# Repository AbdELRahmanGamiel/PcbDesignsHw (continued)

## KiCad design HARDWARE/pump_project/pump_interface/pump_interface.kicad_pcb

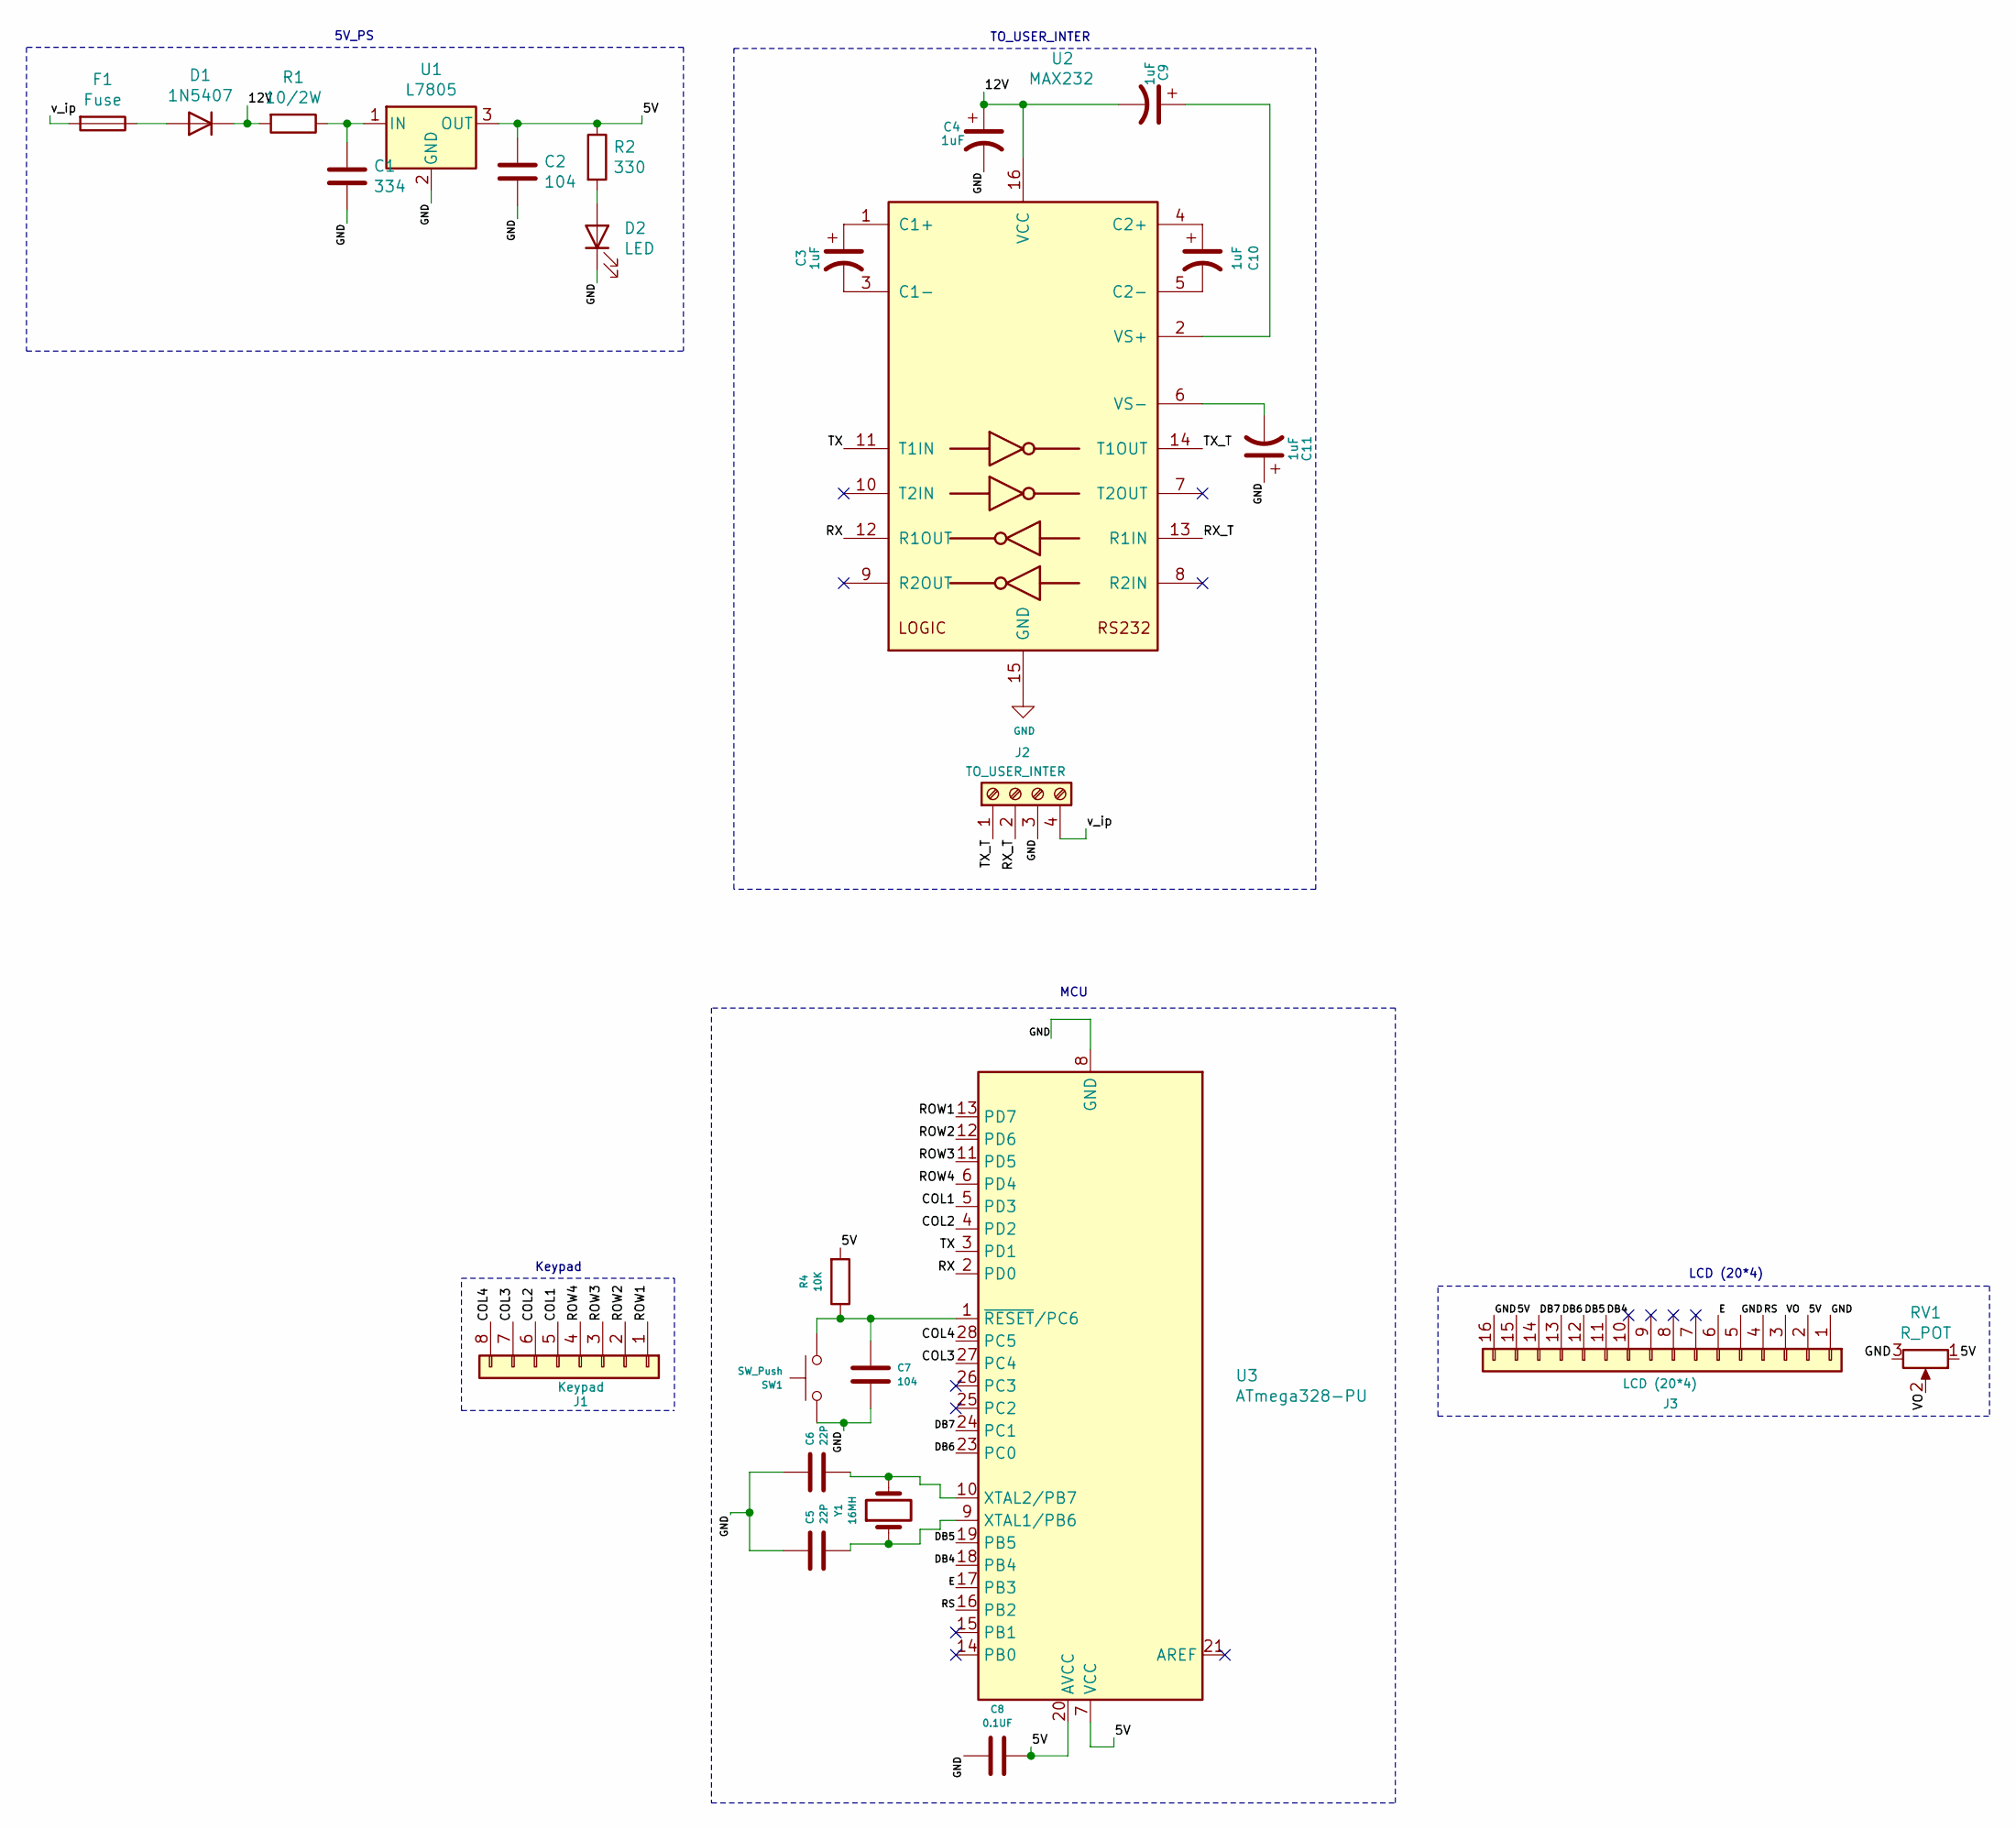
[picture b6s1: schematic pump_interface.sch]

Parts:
C1: 334; C_Disc_D7.0mm_W2.5mm_P5.00mm
C2, C7: 104; C_Disc_D7.0mm_W2.5mm_P5.00mm
C3, C4, C9, C10, C11: 1uF; C_Radial_D5.0mm_H5.0mm_P2.00mm
C5, C6: 22P; C_Disc_D7.0mm_W2.5mm_P5.00mm
C8: 0.1UF; C_Disc_D7.0mm_W2.5mm_P5.00mm
D1: 1N5407; D_DO-201AD_P15.24mm_Horizontal
D2: LED; LED_D5.0mm
F1: Fuse; Fuseholder_Cylinder-5x20mm_Schurter_0031_8201_Horizontal_Op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
J1: Keypad; PinHeader_1x08_P2.54mm_Vertical
J2: TO_USER_INTER; PhoenixContact_MSTBA_2,5_4-G-5,08_1x04_P5.08mm_Horizontal
J3: LCD (20*4); PinHeader_1x16_P2.54mm_Vertical
R1: 10/2W; R_Axial_Power_L20.0mm_W6.4mm_P25.40mm
R2: 330; R_Axial_DIN0207_L6.3mm_D2.5mm_P10.16mm_Horizontal
R4: 10K; R_Axial_DIN0207_L6.3mm_D2.5mm_P10.16mm_Horizontal
RV1: R_POT; Potentiometer_Bourns_3266Y_Vertical
SW1: SW_Push; SW_PUSH_6mm_H7.3mm
U1: L7805; TO-220-3_Vertical
U2: MAX232; DIP-16_W7.62mm_Socket_LongPads
U3: ATmega328-PU; DIP-28_W7.62mm
Y1: 16MH; Resonator-2Pin_W10.0mm_H5.0mm

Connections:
/5V: C2.1, C8.1, J3.2, J3.15, R2.1, R4.2, RV1.1, U1.3 (OUT), U3.7 (VCC), U3.20 (AVCC)
/12V: C4.1, C9.2, D1.1 (K), R1.2, U2.16 (VCC)
/COL1: J1.5, U3.5 (PD3)
/COL2: J1.6, U3.4 (PD2)
/COL3: J1.7, U3.27 (PC4)
/COL4: J1.8, U3.28 (PC5)
/DB4: J3.11, U3.18 (PB4)
/DB5: J3.12, U3.19 (PB5)
/DB6: J3.13, U3.23 (PC0)
/DB7: J3.14, U3.24 (PC1)
/E: J3.6, U3.17 (PB3)
/ROW1: J1.1, U3.13 (PD7)
/ROW2: J1.2, U3.12 (PD6)
/ROW3: J1.3, U3.11 (PD5)
/ROW4: J1.4, U3.6 (PD4)
/RS: J3.4, U3.16 (PB2)
/RX: U2.12 (R1OUT), U3.2 (PD0)
/RX_T: J2.2, U2.13 (R1IN)
/TX: U2.11 (T1IN), U3.3 (PD1)
/TX_T: J2.1, U2.14 (T1OUT)
/VO: J3.3, RV1.2
/v_ip: F1.2, J2.4
GND: C1.2, C2.2, C4.2, C5.2, C6.2, C7.1, C8.2, C11.1, D2.1 (K), J2.3, J3.1, J3.5, J3.16, RV1.3, SW1.1, U1.2 (GND), U2.15 (GND), U3.8 (GND), U3.22 (GND)
unnamed: C1.1, R1.1, U1.1 (IN)
unnamed: C3.1, U2.1 (C1+)
unnamed: C3.2, U2.3 (C1-)
unnamed: C5.1, U3.9 (XTAL1/PB6), Y1.1
unnamed: C6.1, U3.10 (XTAL2/PB7), Y1.2
unnamed: C7.2, R4.1, SW1.2, U3.1 (~RESET~/PC6)
unnamed: C9.1, U2.2 (VS+)
unnamed: C10.1, U2.4 (C2+)
unnamed: C10.2, U2.5 (C2-)
unnamed: C11.2, U2.6 (VS-)
unnamed: D1.2 (A), F1.1
unnamed: D2.2 (A), R2.2

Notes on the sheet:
5V_PS
TO_USER_INTER
MCU
LCD (20*4)
Keypad

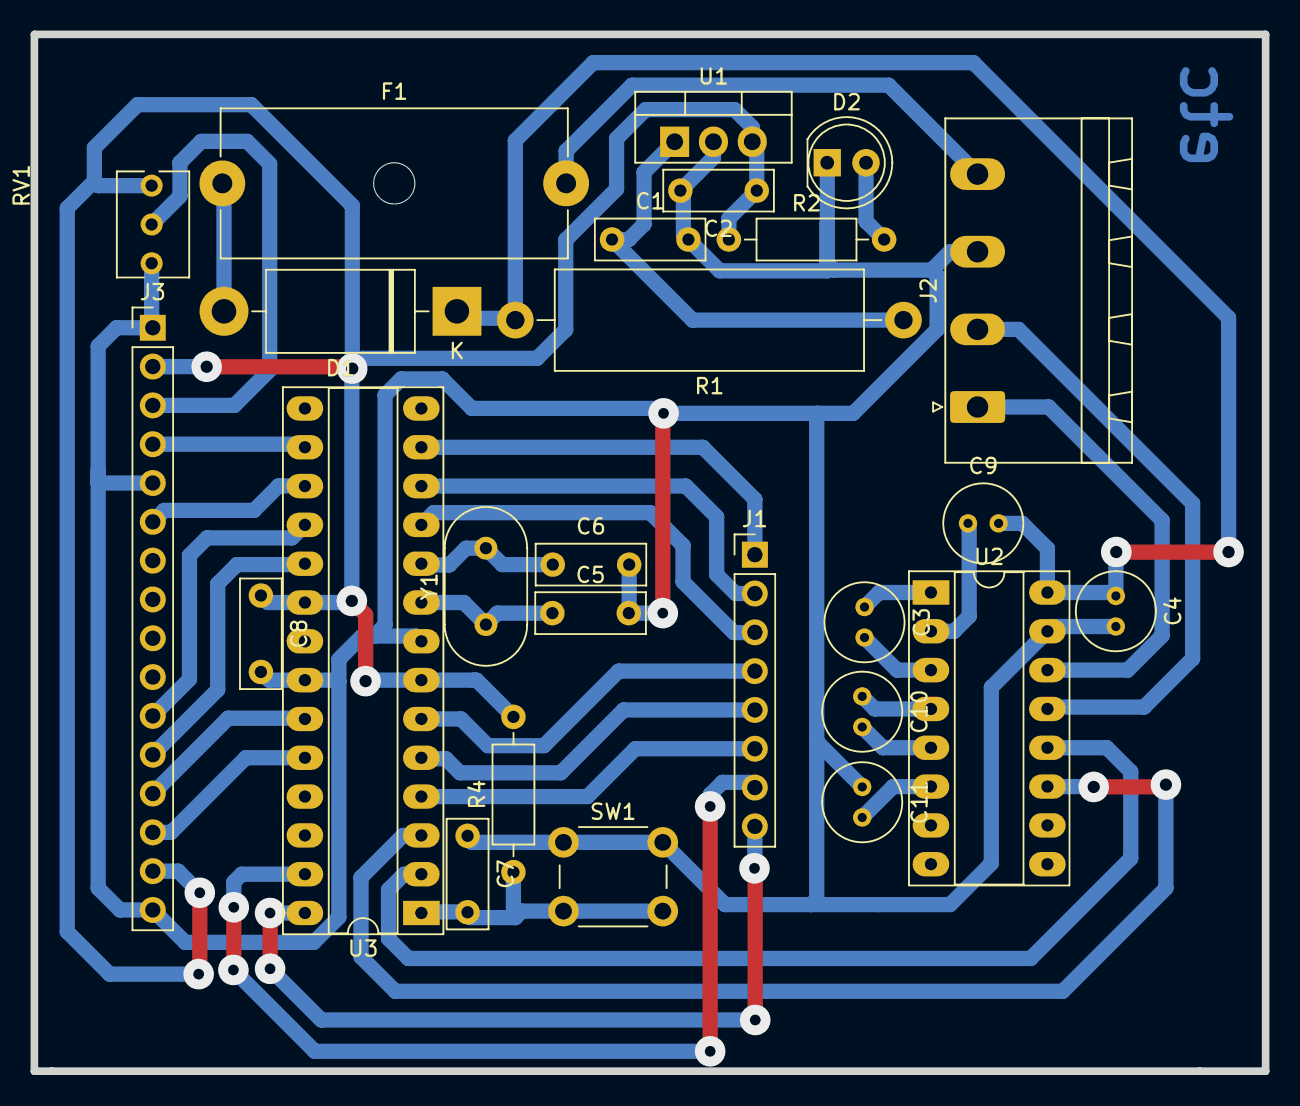
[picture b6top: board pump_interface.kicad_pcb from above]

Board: 2 copper layers, 80.6 x 67.9 mm, 26 parts (0 on the bottom side), 35 nets.
